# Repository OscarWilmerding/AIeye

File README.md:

# AIeye

If you are interested in buying a kit for this fill out this form, if there are enough people I will make and sell kits:
https://forms.gle/SYHFhyDxsT9Xxbqz5
Main repository for the AIeye camera project.

## Supplies

### Parts List
| Name                           | Quantity | Total Price | Link                                                                                                          | Notes                                                                                                                                  |
|--------------------------------|----------|-------------|---------------------------------------------------------------------------------------------------------------|----------------------------------------------------------------------------------------------------------------------------------------|
| Raspberry Pi Zero 2W           | 1        | $26         | [Amazon](https://amzn.to/3Aza8KZ)                                                                             |                                                                                                                                        |
| Display                        | 1        | $18         | [Amazon](https://amzn.to/3WQWfPW)                                                                             |                                                                                                                                        |
| Camera                         | 1        | $9.50       | [Amazon](https://amzn.to/4cCxRY8)                                                                             |                                                                                                                                        |
| Camera Ribbon Cable            | 1        | $9          | [Amazon](https://amzn.to/3AAfSnO)                                                                             | You need this because the Pi Zero has a different ribbon cable than the regular Pi                                                     |
| Custom PCB                     | 1        | $9          | Recommend [PCBWay](https://www.pcbway.com/) or [JLCPCB](https://jlcpcb.com/)                                  | You will need to upload the PCB zip file to the respective website                                                                     |
| PCB Part - Button Power Switch | 1        | $1.85       | [Digi-Key](https://www.digikey.com/en/products/detail/cw-industries/GPTS203211B/3190590)                      |                                                                                                                                        |
| PCB Part - Rotary Encoder      | 1        | $2.60       | [Digi-Key](https://www.digikey.com/en/products/detail/cui-devices/RIC11-22S16D5M-TH/21705934)                 |                                                                                                                                        |
| PCB Part - Alternate Encoder   | *        | *           | [Digi-Key](https://www.digikey.com/en/products/detail/cui-devices/RIC11-22S15D7-TH/21705936)                  | Footprint should be the same for the PCB, but you may need to modify the 3D file for the knob so it fits on the shaft                  |
| PCB Part - Alternate Encoder   | *        | *           | [Digi-Key](https://www.digikey.com/en/products/detail/cui-devices/RIC11-22S13D5S-TH/21705929)                 | Footprint should be the same for the PCB, but you may need to modify the 3D file for the knob so it fits on the shaft                  |
| PCB Part - Voltage Converter   | 1        | $3.95       | [Digi-Key](https://www.digikey.com/en/products/detail/adafruit-industries-llc/4654/12697636)                  |                                                                                                                                        |
| PCB Part - Momentary Button    | 2        | $0.10       | [Digi-Key](https://www.digikey.com/en/products/detail/c-k/PTS636-SK43-LFS/10071716)                           |                                                                                                                                        |
| PCB Part - Female Battery Port | 1        | $0.12       | [Digi-Key](https://www.digikey.com/en/products/detail/jst-sales-america-inc/S2B-PH-K-S/926626)                |                                                                                                                                        |
| Battery                        | 1        | $10.95      | [Digi-Key](https://www.digikey.com/en/products/detail/sparkfun-electronics/PRT-18286/14302550)                |                                                                                                                                        |
| Battery Charger                | 1        | $10.96      | [Amazon](https://amzn.to/3yW2CcH)                                                                             |                                                                                                                                        |

**Total:** ~$102.03  
*Probably will cost 10-20% more with shipping included.*

---

### Other Needed Supplies

| Name                   | Quantity                           | Link                                        | Notes                                                                                                          |
|------------------------|------------------------------------|---------------------------------------------|----------------------------------------------------------------------------------------------------------------|
| 3D Printed Parts       |                                    |                                             |                                                                                                                |
| M3 Screws              | 2 short (5-10mm), 2 long (15-25mm) |                                             | 3D file could be modified for similarly sized screws to fit                                                    |
| Super Glue or Hot Glue |                                    |                                             |                                                                                                                |
| Sandpaper              |                                    |                                             | If you want to improve the surface quality of the prints                                                       |
| Spray Paint            |                                    |                                             | If you are not using colored filament and want to change the surface finish                                    |
| Soldering Iron         |                                    | [Amazon](https://amzn.to/3Z03ozY)          | For making the circuit board                                                                                   |
| Wire                   |                                    |                                             | I used 24 ga, but similarly sized copper wire should work the same (solid core wire may be trickier to solder) |
| MicroSD Card           |                                    | [Amazon](https://amzn.to/4763LuP)          |                                                                                                                |
| SD Card Reader         |                                    |                                             | Some way to read the SD card                                                                                   |

---

### Recommended if You Need to Debug

- **Mini HDMI to HDMI Adapter**
- **Micro USB OTG Adapter**
- **Mouse**
- **Keyboard**

## 3D Printing

- **Layer Height**: 0.2mm
- **Infill**: 10%
- **Printer**: Printed on an Ender 3 S1 (any FDM printer will suffice).
- **Material**: PLA+
- **Supports**: The only parts that require supports are the overhangs above the screen and button panel. I'm using organic supports and forcing the slicer to only generate supports in these areas using the painted support enforcer tool.
- **Orientation**: Some parts are designed to be printed in a specific orientation. Refer to the image below for correct orientations:

## Circuit Board

- **PCB Fabrication**: You'll need to get a custom PCB fabricated; I recommend using PCBway.
- **Soldering Components**: Start by soldering the through-hole components to the board. These are highlighted below. Note how the voltage regulator is mounted slightly off the board. The orientation of the buttons does not matter. Just make sure all the components are soldered to the front side of the board (the side with the text on it).

- **Battery Cord**: Solder wires to the female battery port, and use plenty of shrink wrap to avoid short circuits. When soldering it onto the board, ensure that when the battery is plugged in, the ground goes to the ground pad (the square one). These connectors are easy to mix up and wire backward. It won't damage the device, but if you wire the positive and gnd backwards it will not turn on. The side of the board you solder it to doesn't matter as long as ground goes to ground (square pad). Below is a close-up of the battery connection:

- **5V Connection**: Solder the 5V connection wire to the board. This is soldered on the underside of the board to avoid short circuits if the solder joint faces directly towards the board.
- **Camera Ribbon Cable**: Connect the camera ribbon cable carefully. The port on the Pi is delicate, and if you don't push the plastic piece directly in or out, it can snap off easily.
- **Header Pins**: Solder the header pins onto the Pi and then solder the board onto the Pi. In the image, you’ll see two damaged, dusty pins. These were unnecessary and have been removed from the PCB fab file. The blackboard should connect as far to the right as possible with all of the Pi's header pins still going through the board.
- **5V Connection to Pi**: Solder the 5V connection cord to the back of the Pi. It needs to connect to the 5V pin on the back, not the front, to avoid interference with the screen.

- **Screen Connection**: Press the screen onto the header pins. It should be on the far left of the pins.

- **Testing**: Before placing it in the enclosure, test to ensure everything is working correctly.

## Software/Code

- **Overview**:
  - The project runs on PIOS, which is a slow but functional operating system. It takes a long time to boot up.
  - Once booted, it runs a Python script that displays the camera's GUI using a library called Pygame.

- **Flashing the SD Card**:
  - Use [win32diskimager](https://sourceforge.net/projects/win32diskimager/) to flash the SD card with the camera's code.
  - Download win32diskimager.
  - Download the `.img` file from my repository. 
    - https://drive.google.com/drive/folders/1noxVPlFzV9c3eGpXCnVfaX7x1-svAIYr?usp=sharing
  - Within win32diskimager, select your SD card, then select your downloaded image and click write. This process can take 10-30 minutes.
  
- **Configuring the SD Card**:
  - Once the image is flashed, remove the SD card and reinsert it into your computer.
  - Open the drive from your computor, and you should see a few folders. Many of the files are folders that the Raspberry Pi will rely on when it boots.
  - There should be a folder called `wifi credentials`, edit the text file and replace the credentials with the wifi credentials you wish the camera to use.
    - You can add your home Wi-Fi later, but not at this point.
    - You can make these credentials your mobile hotspot so you can take the camera outside your house. If you don’t want it to leave your house, just add your home Wi-Fi.
    - You can replace these credentials with a second or third Wi-Fi network once you've booted up the camera and loaded them into memory, which I'll cover later.
    - Be warned mobile hotspots can be annoying to connect to from the Pi, in my experience my Iphone hotspot was far less reliable than my home wifi.
  - Notice the folder called the photos, you dont need to do anything with it now but this is where the photos are going to be saved to so if you want to take the photos off the camera then that's where you get them.
    
- **API Keys**:
  - In the folder labeled `API keys`, you'll need to enter two API keys: one for Astica and one for OpenAI. You only need to input the keys once; the program will pull from that file every time it runs.
    - To get the Astica API key, go to [Astica AI](https://astica.ai/).
    - You'll need to add funds to Vision Compute. I recommend adding $10. Each image costs roughly $0.03 for Astica and OpenAI, so about $0.06 per image.
    - For the OpenAI key, go to [OpenAI Platform](https://platform.openai.com/settings/profile?tab=api-keys).
    - You'll need to create a user API key, which is now considered legacy. I recommend adding $10 to it as well.
    
- **Final Steps**:
  - Once you’ve added the API keys to the text file, you should be all set! Plug in the battery and power it on with the large button.
  - Once fully booted, press the middle button to open the settings menu, then press the knob to load the Wi-Fi settings. If you find that the camera is taking photos that are 90° or 180° off, go to the second menu in the settings and click rotate 90 degrees.
  - If you want to get the photos off of the pi then remove the sd card, plug it in your computor, and all the photos should be in the folder called photos.

- **Controls:**
  - When the "a normal photo" screen is being displayed this is the home screen, press the knob in to take a photo. Rotate the knob to change what the descriptor is for the photo you are taking.
  - Leftmost button is the power switch, you will need to press it more than the other 2 buttons to get it to click.
  - Middle button is settings
    - Once in the settings twist the know to navigate to which setting you want to do. When you press the knob in it will load the setting. 
  - Right button is playback. Press it and you will be able to see all the photos you have already taken. Press it again to go back to the screen with the descriptor sentence where you can take the photo.

## Debugging

- **Troubleshooting**:
  - If you ever need to login (which you shouldent), then the username is oewil and the password is 23309th. no I dont use that username or password anywhere else.
  - If something isn’t working, you'll need to connect to the Pi directly. You can do this by opening the bottom and plugging a mini HDMI cable and keyboard into the Pi. Alternatively, you can connect to the Pi via VNC Viewer. Note that you will not be able to connect to the Pi via VNC Viewer if it isn’t connected to the internet.
  - once you connect to the pi via vnc viewer you will need to press the escape key to ente the desktop
  - I have also included an image for the camera where the drivers to make it fit to the screen are not included. This may be easier to modify code as the screen will not be small on the VNC viewer.
  - You should also use this if you want to upgrade the screen.
  - If you want to run the script without booting on the entire camera, you are going to need to go to the terminal and run the command: sudo -E python3 cam_v3.py

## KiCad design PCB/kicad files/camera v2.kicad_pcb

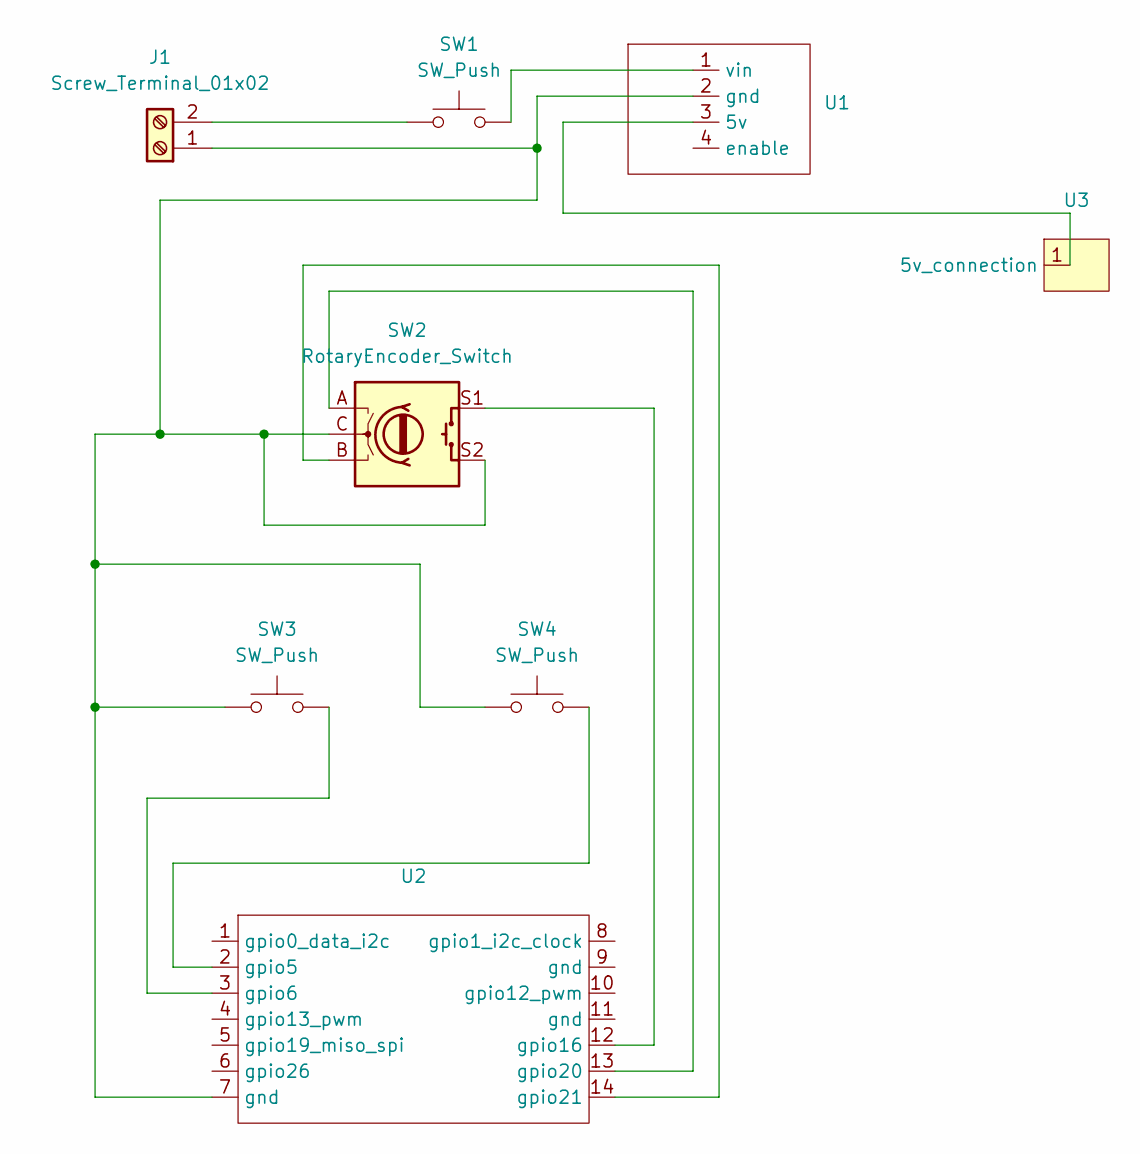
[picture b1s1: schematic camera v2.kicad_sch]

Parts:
J1: Screw_Terminal_01x02; connection for jst wires
SW1: SW_Push; button switch
SW2: RotaryEncoder_Switch; encoder
SW3, SW4: SW_Push; button
U1: mini boost
U2: pi segment
U3: 5v connection

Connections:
unnamed: J1.1, SW2.C, SW2.S2, SW3.1, SW4.1, U1.2 (gnd), U2.7 (gnd)
unnamed: J1.2, SW1.1
unnamed: U1.3 (5v), U3.1 (5v_connection)
unnamed: SW1.2, U1.1 (vin)
unnamed: SW4.2, U2.2 (gpio5)
unnamed: SW3.2, U2.3 (gpio6)
unnamed: SW2.S1, U2.12 (gpio16)
unnamed: SW2.A, U2.13 (gpio20)
unnamed: SW2.B, U2.14 (gpio21)

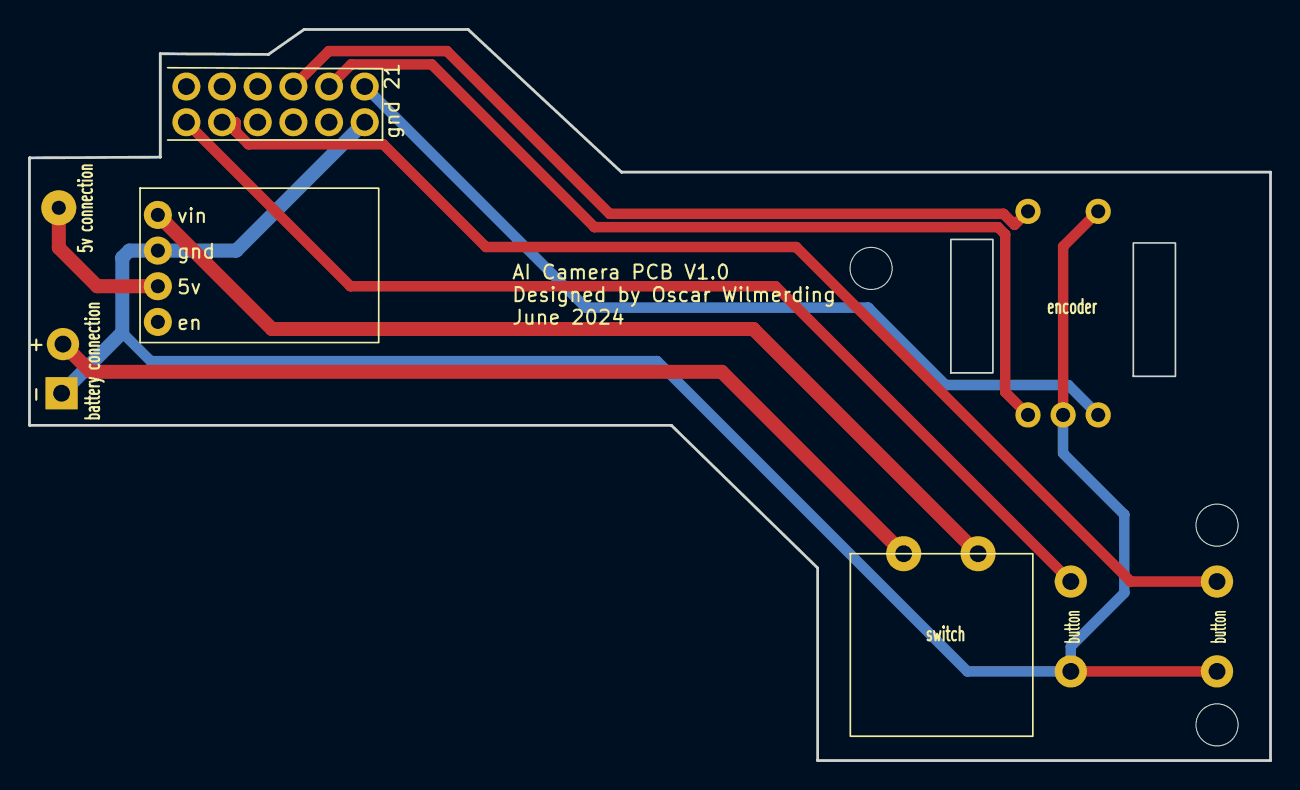
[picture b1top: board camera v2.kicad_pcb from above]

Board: 2 copper layers, 88.4 x 52.1 mm, 8 parts (0 on the bottom side), 9 nets.
